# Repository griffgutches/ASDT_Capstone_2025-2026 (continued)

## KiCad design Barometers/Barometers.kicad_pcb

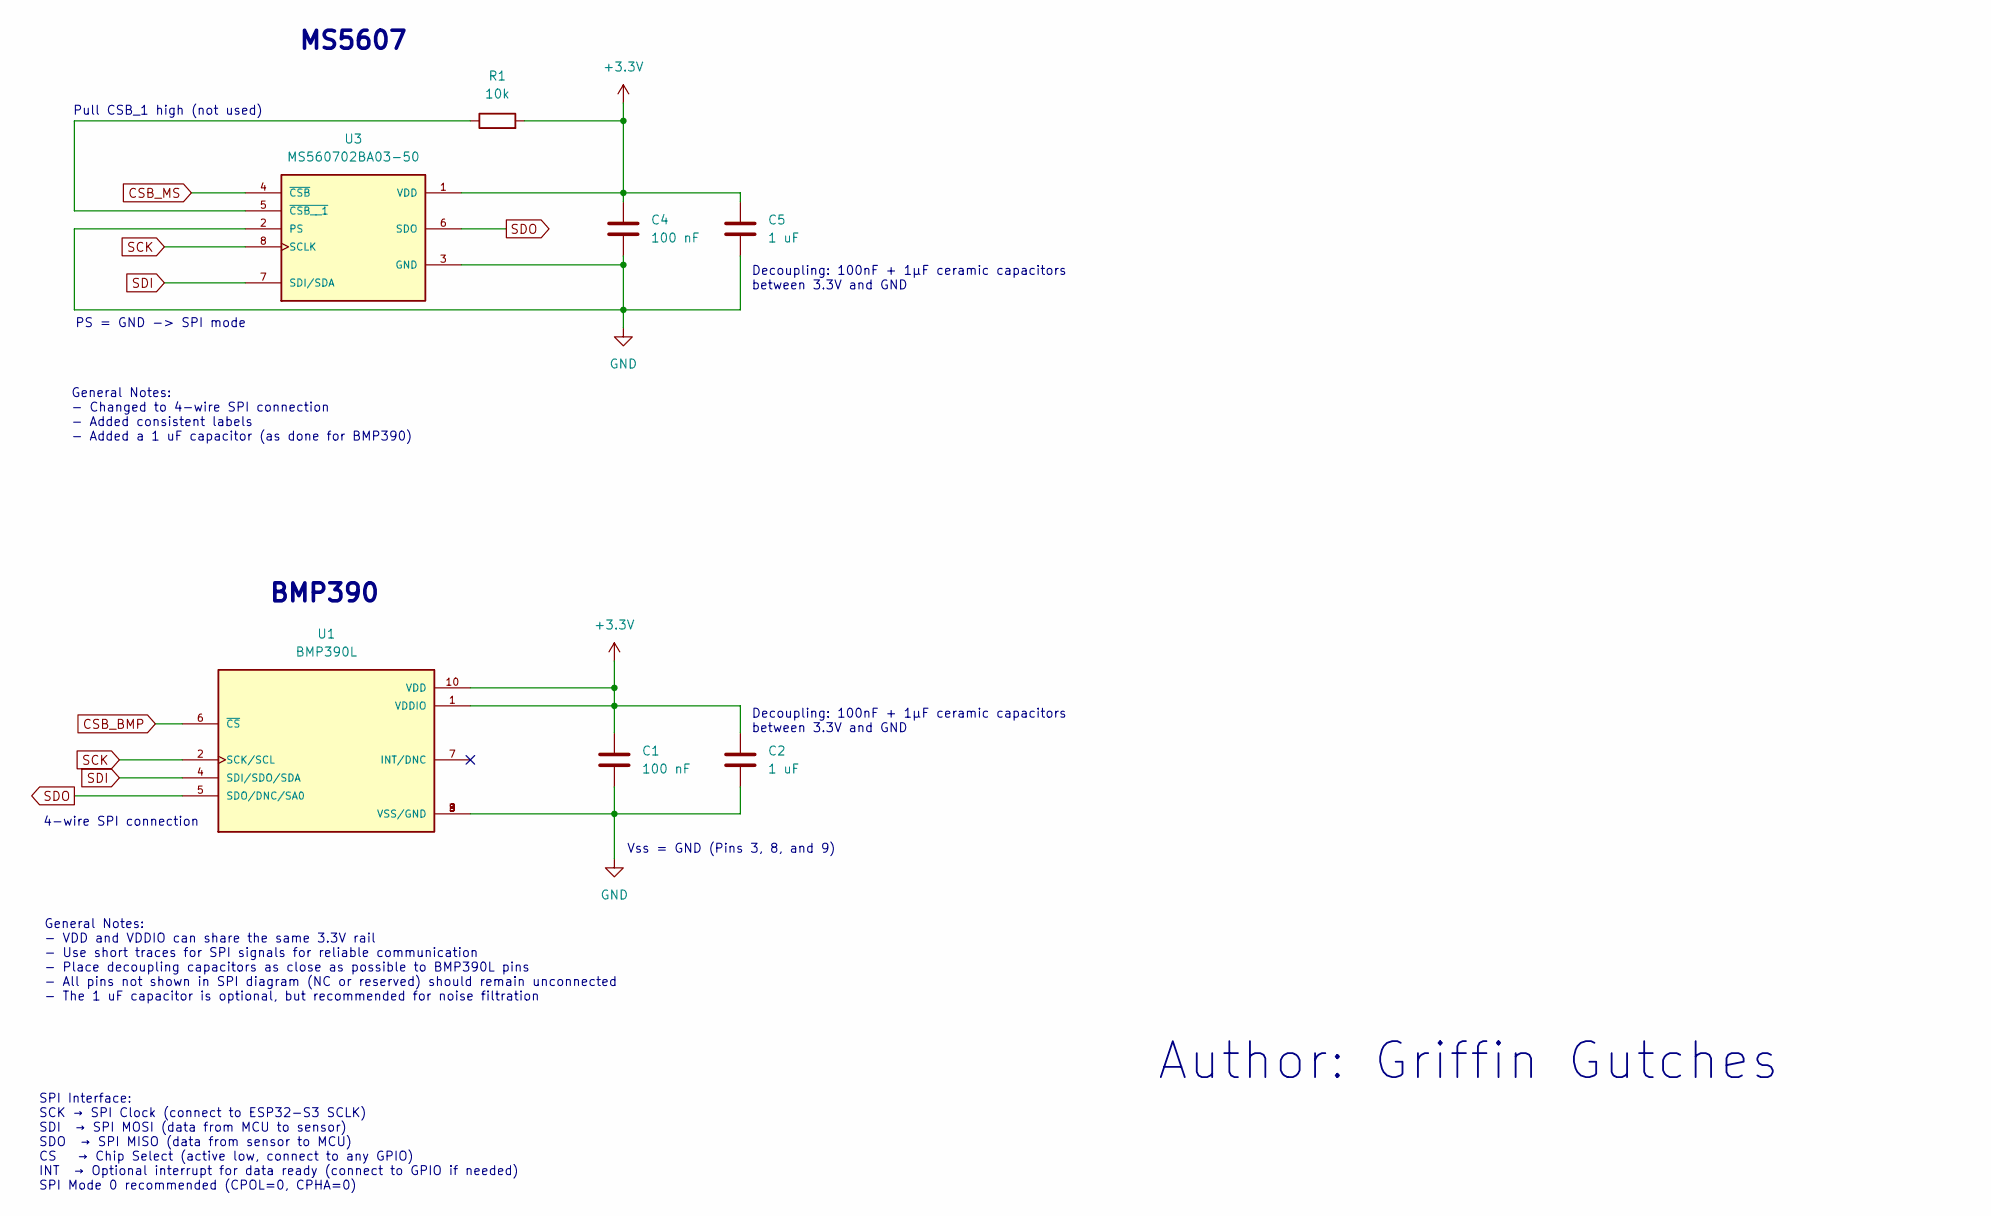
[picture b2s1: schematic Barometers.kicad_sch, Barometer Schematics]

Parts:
C1, C4: 100 nF; C_0402_1005Metric
C2, C5: 1 uF; C_0402_1005Metric
R1: 10k; R_0402_1005Metric
U1: BMP390L; XDCR_BMP390L; PARTREV 1.7
U3: MS560702BA03-50; XDCR_LSM6DSO32TR

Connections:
+3.3V: C1.1, C2.1, C4.1, C5.1, R1.2, U1.1 (VDDIO), U1.10 (VDD), U3.1 (VDD)
CSB_BMP: U1.6 (~CS)
CSB_MS: U3.4 (~CSB)
GND: C1.2, C2.2, C4.2, C5.2, U1.3 (VSS/GND), U1.8 (VSS/GND), U1.9 (VSS/GND), U3.2 (PS), U3.3 (GND)
unnamed: R1.1, U3.5 (~CSB__1)
SCK: U1.2 (SCK/SCL), U3.8 (SCLK)
SDI: U1.4 (SDI/SDO/SDA), U3.7 (SDI/SDA)
SDO: U1.5 (SDO/DNC/SA0), U3.6 (SDO)

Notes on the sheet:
Decoupling: 100nF + 1µF ceramic capacitors between 3.3V and GND
PS = GND -> SPI mode
MS5607
Vss = GND (Pins 3, 8, and 9)
General Notes: - VDD and VDDIO can share the same 3.3V rail - Use short traces for SPI signals for reliable communication - Place decoupling capacitors as close as possible to BMP390L pins - All pins not shown in SPI diagram (NC or reserved) should remain unconnected - The 1 uF capacitor is optiona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
Pull CSB_1 high (not used)
Author: Griffin Gutches
SPI Interface: SCK → SPI Clock (connect to ESP32-S3 SCLK) SDI → SPI MOSI (data from MCU to sensor) SDO → SPI MISO (data from sensor to MCU) CS → Chip Select (active low, connect to any GPIO) INT → Optional interrupt for data ready (connect to GPIO if needed) SPI Mode 0 recommended (CPOL=0, CPHA=0)
BMP390
4-wire SPI connection
General Notes: - Changed to 4-wire SPI connection - Added consistent labels - Added a 1 uF capacitor (as done for BMP390)

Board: 2 copper layers, 7 parts (0 on the bottom side), 6 nets, no tracks yet.

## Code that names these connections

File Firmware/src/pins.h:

#pragma once


#define MS5607_CS              1
#define BMP390_CS              2
#define MAG_CS                 4
#define RADIO_CS               7
#define BMI088_GYRO_CS         14
#define ADXL375_IMU_CS         21
#define BMI088_ACCEL_CS        40
#define ISM6HG256X_IMU_CS      41

#define ADXL375_INT            11
#define RADIO_INT              13
#define BMI088_ACCEL_INT       18
#define GPS_INT                31
#define MMC598_MAG_INT         42

#define SPI_MISO               10
#define SPI_SCK                17
#define SPI_MOSI               44
#define I2C_SCL                45
#define I2C_SDA                46

#define FLASH_I03              25
#define FLASH_I02              26
#define FLASH_CS               27
#define FLASH_CLK              28
#define FLASH_IO1              29
#define FLASH_IO0              30

#define SD_CMD                 35
#define SD_DATA_0              37
#define SD_DATA_1              38
#define SD_DATA_2              33
#define SD_DATA_3              34
#define SD_CLOCK               36

#define TIMEPULSE              8
#define BATTERY_SENSE          9
#define BUZZER                 39
#define ANT_SW                 43
#define RADIO_BUSY             6

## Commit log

2025-11-01 Create test
2025-11-01 Commit Initial Schematic Files
2025-11-01 add gps schem
2025-11-01 Imported Barometer Into Main Branch
2025-11-01 add whole project file
2025-11-01 Sub-schematics Generated
2025-11-01 add gps sensor
2025-11-01 Radio Layout V1.0
2025-11-01 Saved Changes
2025-11-01 esp32 schem add
2025-11-03 testing lock
2025-11-07 esp32 edits
2025-11-08 minor updates
2025-11-08 Aggregated sub schematics into single primary schematic
2025-11-09 add I/O to GPS sheet
2025-11-09 remove old esp/gps files
2025-11-15 add more I/O to MCU
2025-11-15 Organization and LSM6DSO32 (IMU) schematic
2025-11-15 Rename IMU to IMUs since we will be using two IMUs now.
2025-11-15 Added first IMU schematic.
2025-11-15 Added second IMU schematic.
2025-11-15 Simplified Naming Convention
2025-11-15 update changes to MCU, add gitignore
2025-11-15 add to gitignore
2025-11-15 tidy git
2025-11-16 add footprint/LCSC to parts
2025-11-16 make DIO2 local
2025-11-16 update sheet pins
2025-11-16 add more footprints
2025-11-21 added footprints to barometer project
2025-11-21 Barometer layout draft created
2025-11-22 adding labels and updating IMU sch
2025-11-22 update MCU
2025-11-22 add CS's
2025-11-22 Added NT2016 TCXO Symbol and Footprint
    Added NT2016 TCXO Symbol and Footprint
2025-11-22 Magnetometer Footprint Added
    Magnetometer Footprint Added
2025-11-22 synced sheet pins in Data_Logger_Board_pro
2025-11-22 added pwr schematic.
2025-11-22 update IO
2025-11-22 Updated pwr labels and sheet pins
2025-11-23 Revert "Updated pwr labels and sheet pins"
    This reverts commit 1a9ac38adf7d5b931f8e0b911fe1764f57823125.
2025-11-23 diode part#
2025-11-29 rem old files and add LCSC #'s
2025-12-04 update pcb and create .bkp backup
2025-12-04 Layout for LoRa Radio
2025-12-05 partial MCU layout
2025-12-05 more progress on MCU layout
2025-12-05 more MCU layout
2025-12-05 reorg board for pictures
2025-12-05 fix footprint errors
2025-12-06 add microSD
2025-12-07 footprint + sd tweaks
2026-01-06 update footprint
2026-01-09 move sd
2026-01-10 Floor Planned PCB layout
2026-01-10 add WiFi 3D model
2026-01-10 add more 3dmodels
2026-01-10 more 3dmodels
2026-01-10 more models
2026-01-10 schem updates
2026-01-16 place LDO
2026-01-16 layout updates
2026-01-17 Layout
    Fixed via sizing, routed fanout from ESP
2026-01-22 more layout
2026-01-23 save point
2026-01-23 layout power plane
2026-01-23 update back plane fill settings
2026-01-23 fix BMI footprint and resolve some errors
2026-01-23 addition
2026-01-24 Updates to board routing
    Added SMA connector for radio, added additional SPI routing. Reworked some routing for other modules.
2026-01-25 layout
    fix rf, usb netclass, add timepulse, round dimensions to even number, re-route GPS, 22 ohm in usb line, buttons to front, reg to front, change solder jumper for conn
2026-01-28 round corners, place mounting holes
2026-01-30 finish SPI routing +silkscreen tidy
2026-01-31 add stitching vias
2026-01-31 Corrected DRC Errors
    Added 220Ohm resistor to TCXO output.
    Fixed DRC Errors
    Added stitching vias
2026-01-31 fix missing gnd
2026-01-31 fix gps line
2026-02-01 review LCSC fields
2026-02-01 update pcb from schem
2026-02-02 space mounting holes
2026-02-02 schematic recs
2026-02-03 fix battery sense + AIAA logo
2026-02-03 logo trails
2026-02-04 add gnd vias below antenna
2026-02-04 Corrected RF Switch polarity
2026-02-04 Img, MP1, INu2
2026-02-05 remove units for extraction
2026-02-05 fix netclass and rm bkp
2026-02-05 four layer creation
2026-02-05 start power routing
2026-02-05 ready for review
2026-02-05 fix connections
2026-02-06 fix silkscreen
2026-02-06 fix merge
2026-02-06 3v3 routing with fat traces
2026-02-07 remove extra vias, tidy silkscreen warnings
2026-02-07 add parallel vias
2026-02-07 add more stitching vias
2026-02-07 fix silk and re-align drill holes
2026-02-09 readd thermal reliefs
2026-02-10 add tooling holes, rm mt hole symbol
2026-02-13 match trace widths to 4 layer
2026-02-14 start firmware
2026-02-15 adjust functionality of sd
2026-02-16 add readme
2026-02-18 add sd functionality and python binary encoder
2026-02-19 Start updating GPIO pinout
    Updated GPIO pinout information in README.
2026-02-20 ESP32 adaptation
2026-02-25 Update GPIO pinout information in README
2026-02-25 fix formatting
2026-02-27 code for demo
2026-03-21 Fix pin typo
2026-03-21 update for esp32 implementation
2026-03-21 fix gpio pins
2026-03-21 update more for esp32
2026-05-02 runs on esp32
